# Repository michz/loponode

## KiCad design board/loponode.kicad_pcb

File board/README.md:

LoPoNode
========

Attribution
-----------

Thanks to snapeda.com for providing a footprint of TPS61322.

License
-------

Creative Commons Attribution 4.0

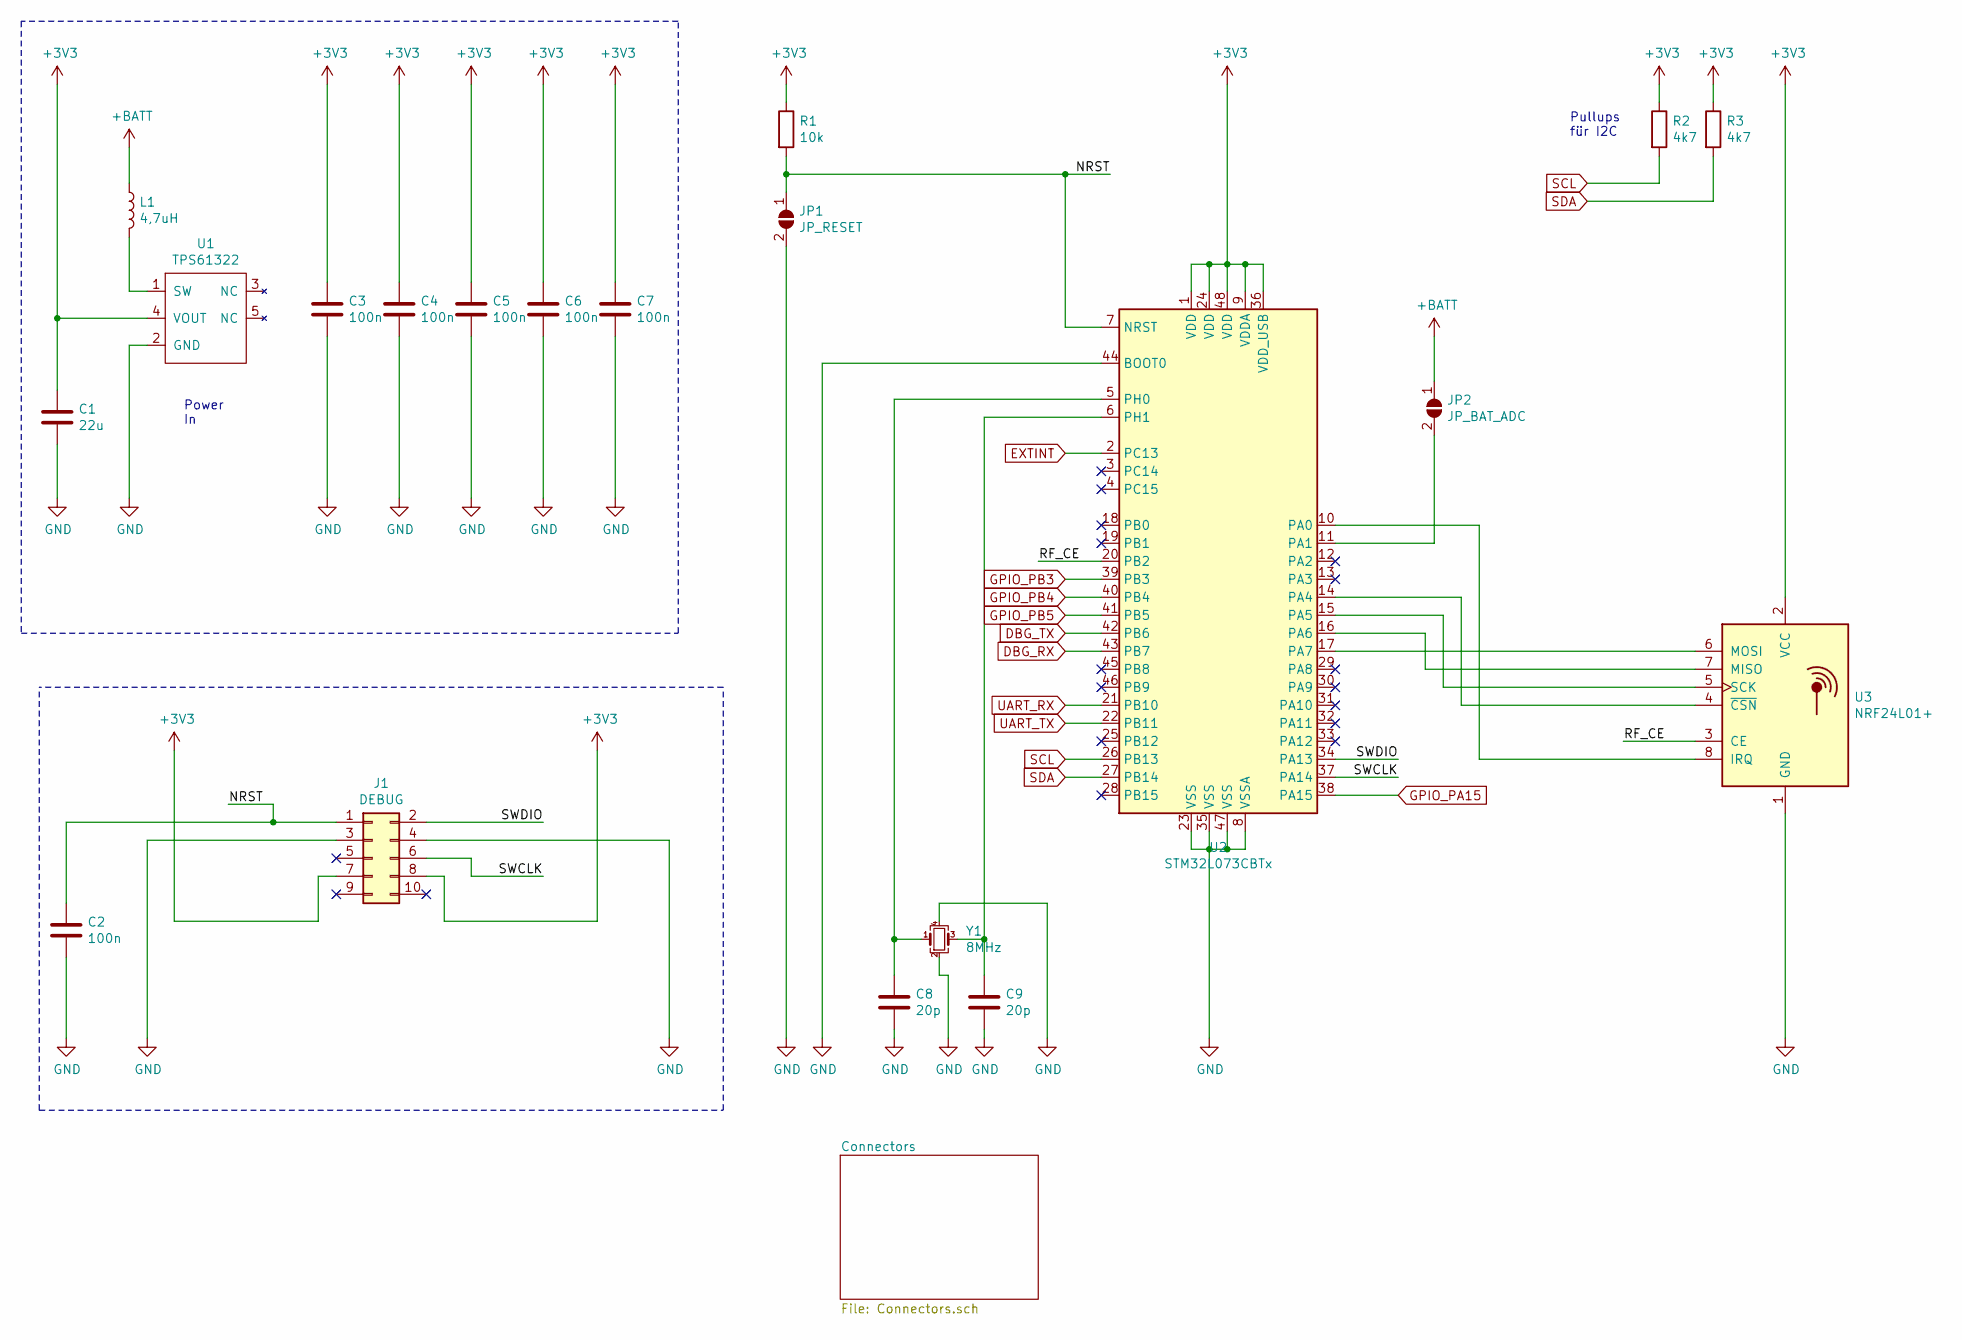
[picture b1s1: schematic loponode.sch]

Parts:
C1: 22u; C_0805_2012Metric_Pad1.15x1.40mm_HandSolder
C2, C3, C4, C5, C6, C7: 100n; C_0805_2012Metric_Pad1.15x1.40mm_HandSolder
C8, C9: 20p; C_0805_2012Metric_Pad1.15x1.40mm_HandSolder
J1: DEBUG; PinHeader_2x05_P2.54mm_Vertical
JP1: JP_RESET; SolderJumper-2_P1.3mm_Open_TrianglePad1.0x1.5mm
JP2: JP_BAT_ADC; SolderJumper-2_P1.3mm_Open_TrianglePad1.0x1.5mm
L1: 4,7uH; L_1210_3225Metric_Pad1.42x2.65mm_HandSolder
R1: 10k; R_0805_2012Metric_Pad1.15x1.40mm_HandSolder
R2, R3: 4k7; R_0805_2012Metric_Pad1.15x1.40mm_HandSolder
U1: TPS61322; SOT95P280X145-5N
U2: STM32L073CBTx; LQFP-48_7x7mm_P0.5mm
U3: NRF24L01+; nRF24L01_Breakout
Y1: 8MHz; Crystal_SMD_EuroQuartz_MQ-4Pin_7.0x5.0mm_HandSoldering

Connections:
+3V3: C1.1, C3.1, C4.1, C5.1, C6.1, C7.1, J1.7, J1.8, R1.1, R2.1, R3.1, U1.4 (VOUT), U2.1 (VDD), U2.9 (VDDA), U2.24 (VDD), U2.36 (VDD_USB), U2.48 (VDD), U3.2 (VCC); also elsewhere on the board
+BATT: JP2.1 (A), L1.1; also elsewhere on the board
/NRST: C2.1, J1.1, JP1.1 (A), R1.2, U2.7 (NRST)
/RF_CE: U2.20 (PB2), U3.3 (CE)
/SWCLK: J1.6, U2.37 (PA14)
/SWDIO: J1.2, U2.34 (PA13)
DBG_RX: U2.43 (PB7); also elsewhere on the board
DBG_TX: U2.42 (PB6); also elsewhere on the board
EXTINT: U2.2 (PC13); also elsewhere on the board
GND: C1.2, C2.2, C3.2, C4.2, C5.2, C6.2, C7.2, C8.2, C9.2, J1.3, J1.4, JP1.2 (B), U1.2 (GND), U2.8 (VSSA), U2.23 (VSS), U2.35 (VSS), U2.44 (BOOT0), U2.47 (VSS), U3.1 (GND), Y1.2, Y1.4; also elsewhere on the board
GPIO_PA15: U2.38 (PA15); also elsewhere on the board
GPIO_PB3: U2.39 (PB3); also elsewhere on the board
GPIO_PB4: U2.40 (PB4); also elsewhere on the board
GPIO_PB5: U2.41 (PB5); also elsewhere on the board
unnamed: C8.1, U2.5 (PH0), Y1.1
unnamed: C9.1, U2.6 (PH1), Y1.3
unnamed: JP2.2 (B), U2.11 (PA1)
unnamed: L1.2, U1.1 (SW)
unnamed: U2.10 (PA0), U3.8 (IRQ)
unnamed: U2.14 (PA4), U3.4 (~CSN)
unnamed: U2.15 (PA5), U3.5 (SCK)
unnamed: U2.16 (PA6), U3.7 (MISO)
unnamed: U2.17 (PA7), U3.6 (MOSI)
SCL: R2.2, U2.26 (PB13); also elsewhere on the board
SDA: R3.2, U2.27 (PB14); also elsewhere on the board
UART_RX: U2.21 (PB10); also elsewhere on the board
UART_TX: U2.22 (PB11); also elsewhere on the board

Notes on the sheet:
Pullups für I2C
Power In

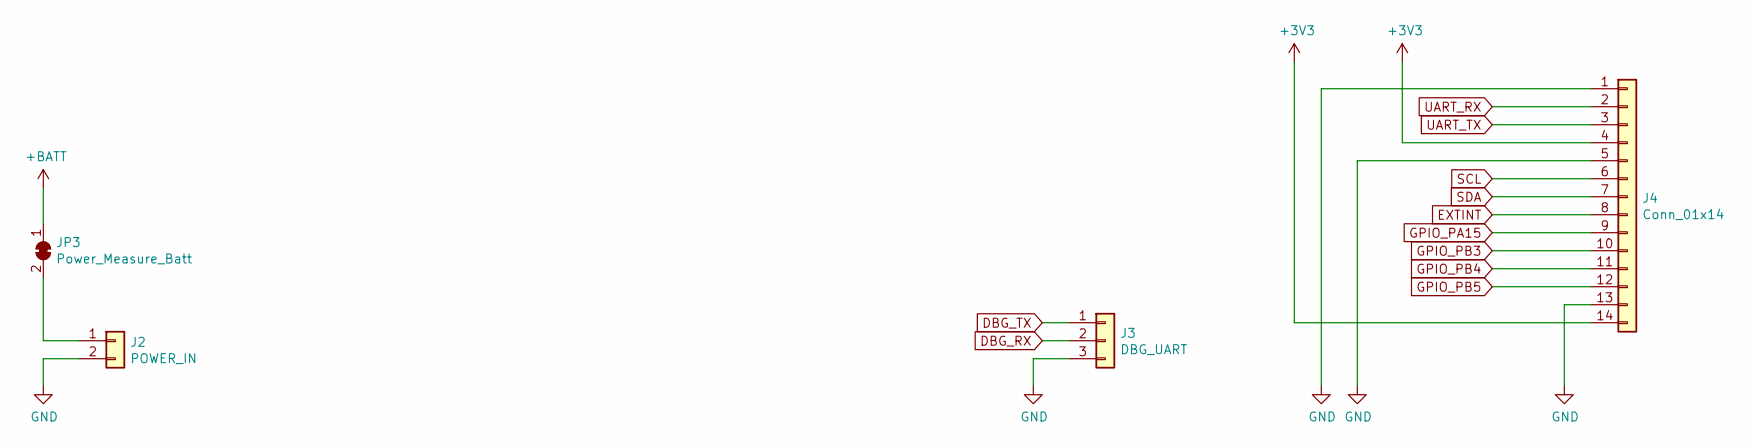
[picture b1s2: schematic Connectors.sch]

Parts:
J2: POWER_IN; PinHeader_1x02_P2.54mm_Vertical
J3: DBG_UART; PinHeader_1x03_P2.54mm_Vertical
J4: Conn_01x14; PinHeader_1x14_P2.54mm_Vertical
JP3: Power_Measure_Batt; SolderJumper-2_P1.3mm_Bridged_Pad1.0x1.5mm

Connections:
+3V3: J4.4, J4.14; also elsewhere on the board
+BATT: JP3.1 (A); also elsewhere on the board
DBG_RX: J3.2; also elsewhere on the board
DBG_TX: J3.1; also elsewhere on the board
EXTINT: J4.8; also elsewhere on the board
GND: J2.2, J3.3, J4.1, J4.5, J4.13; also elsewhere on the board
GPIO_PA15: J4.9; also elsewhere on the board
GPIO_PB3: J4.10; also elsewhere on the board
GPIO_PB4: J4.11; also elsewhere on the board
GPIO_PB5: J4.12; also elsewhere on the board
unnamed: J2.1, JP3.2 (B)
SCL: J4.6; also elsewhere on the board
SDA: J4.7; also elsewhere on the board
UART_RX: J4.2; also elsewhere on the board
UART_TX: J4.3; also elsewhere on the board

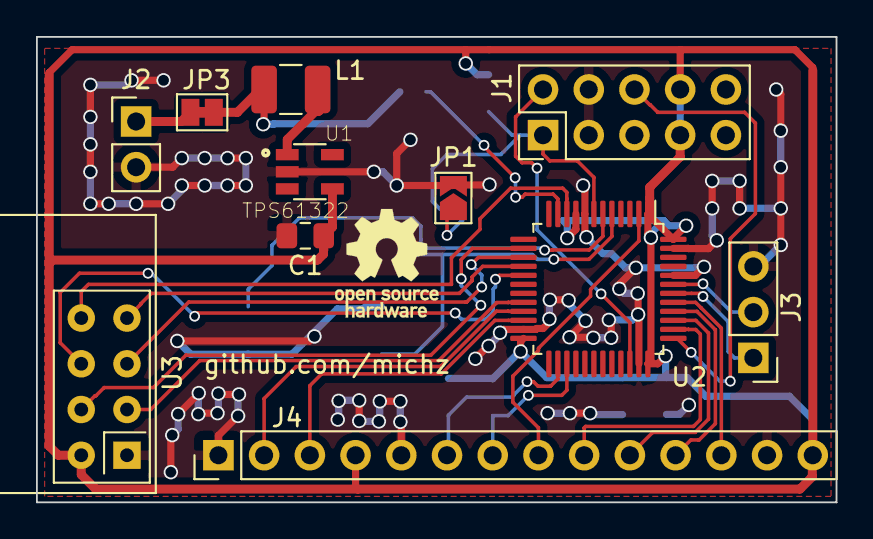
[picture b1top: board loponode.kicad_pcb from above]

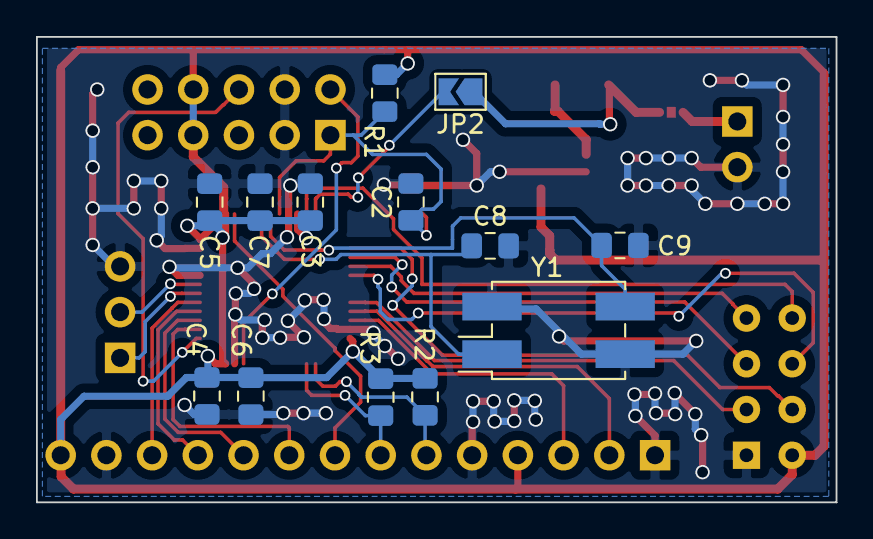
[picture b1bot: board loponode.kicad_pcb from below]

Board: 2 copper layers, 44.4 x 25.9 mm, 24 parts (13 on the bottom side), 28 nets.

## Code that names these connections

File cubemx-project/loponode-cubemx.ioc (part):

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Mcu.Name=STM32L073C(B-Z)Tx
Mcu.Package=LQFP48
Mcu.UserName=STM32L073CBTx
PA0.Mode=SYS_WakeUp0
PA0.Signal=SYS_WKUP1
PA1.Mode=IN1
PA1.Signal=ADC_IN1
PA13.Mode=Serial_Wire
PA13.Signal=SYS_SWDIO
PA14.Mode=Serial_Wire
PA14.Signal=SYS_SWCLK
PA15.Signal=GPIO_Analog
PA4.Signal=SPI1_NSS
PA5.Signal=SPI1_SCK
PA6.Signal=SPI1_MISO
PA7.Signal=SPI1_MOSI
PB10.Signal=LPUART1_RX
PB11.Signal=LPUART1_TX
PB13.Mode=I2C
PB13.Signal=I2C2_SCL
PB14.Mode=I2C
PB14.Signal=I2C2_SDA
PB2.Signal=GPIO_Output
PB3.Signal=GPIO_Analog
PB4.Signal=GPIO_Analog
PB5.Signal=GPIO_Analog
PB6.Signal=USART1_TX
PB7.Signal=USART1_RX
PC13.Mode=SYS_WakeUp1
PC13.Signal=SYS_WKUP2
PH0-OSC_IN.Mode=HSE-External-Oscillator
PH0-OSC_IN.Signal=RCC_OSC_IN
PH1-OSC_OUT.Mode=HSE-External-Oscillator
PH1-OSC_OUT.Signal=RCC_OSC_OUT
RCC.HSE_VALUE=8000000
RCC.SYSCLKFreq_VALUE=8000000
RCC.SYSCLKSource=RCC_SYSCLKSOURCE_HSE
board=custom

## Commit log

2019-06-26 readme added
2019-06-26 add (no finished) first tries
2019-06-27 some fixes, annotations, associations
2019-06-29 add jumper for power measurement; format GND a bit better
2019-06-29 some more annotations
2019-06-29 do some first layout
2019-06-29 add some wires
2019-06-30 many optimizations; LAYOUT!
2019-07-06 new directory structure
    * subfolder for board (KiCAD)
    * subfolder for stm cubemx project
    * subfolder for firmware (empty yet)
2019-07-06 move open hardware marking
    + fix some absolute path manually
2019-07-06 place some labels better
2019-07-06 do some exports of layout and schematics
2019-07-06 rename directory for better consistency
